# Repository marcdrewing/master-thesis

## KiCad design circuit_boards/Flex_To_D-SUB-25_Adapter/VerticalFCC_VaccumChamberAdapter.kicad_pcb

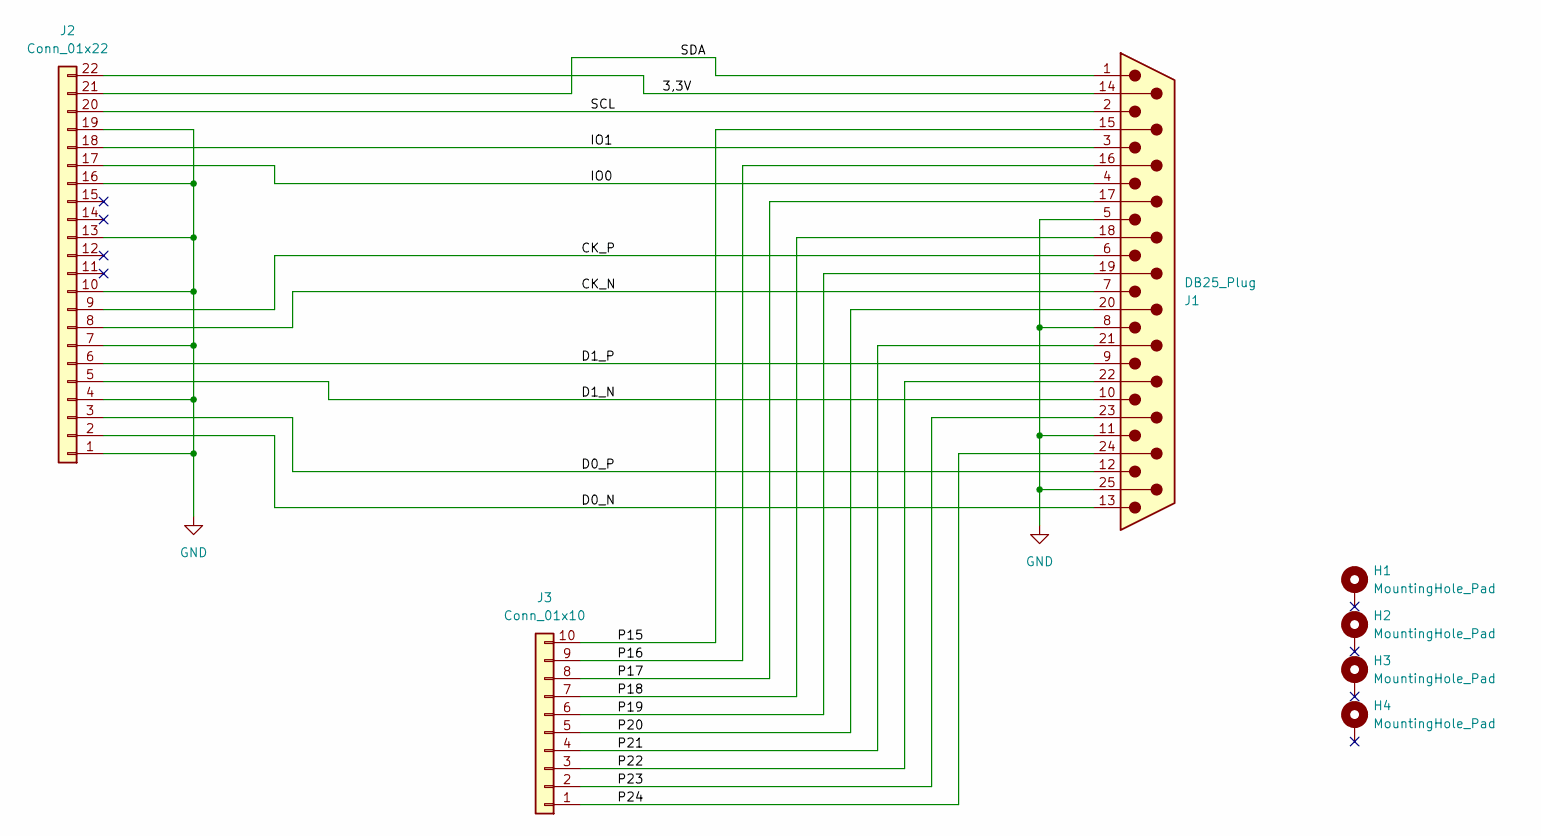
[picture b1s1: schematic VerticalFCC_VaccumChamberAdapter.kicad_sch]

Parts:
H1, H2, H3, H4: MountingHole_Pad; MountingHole_2.5mm_Pad
J1: DB25_Plug; D-Sub 25 Platine Buchse
J2: Conn_01x22; 22P 0.5mm Vertical FPC FFC Flat Cable Connector
J3: Conn_01x10; PinHeader_1x10_P2.54mm_Vertical

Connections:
/3,3V: J1.14, J2.22
/CK_N: J1.7, J2.8
/CK_P: J1.6, J2.9
/D0_N: J1.13, J2.2
/D0_P: J1.12, J2.3
/D1_N: J1.10, J2.5
/D1_P: J1.9, J2.6
/IO0: J1.4, J2.17
/IO1: J1.3, J2.18
/P15: J1.15, J3.10
/P16: J1.16, J3.9
/P17: J1.17, J3.8
/P18: J1.18, J3.7
/P19: J1.19, J3.6
/P20: J1.20, J3.5
/P21: J1.21, J3.4
/P22: J1.22, J3.3
/P23: J1.23, J3.2
/P24: J1.24, J3.1
/SCL: J1.2, J2.20
/SDA: J1.1, J2.21
GND: J1.5, J1.8, J1.11, J1.25, J2.1, J2.4, J2.7, J2.10, J2.13, J2.16, J2.19

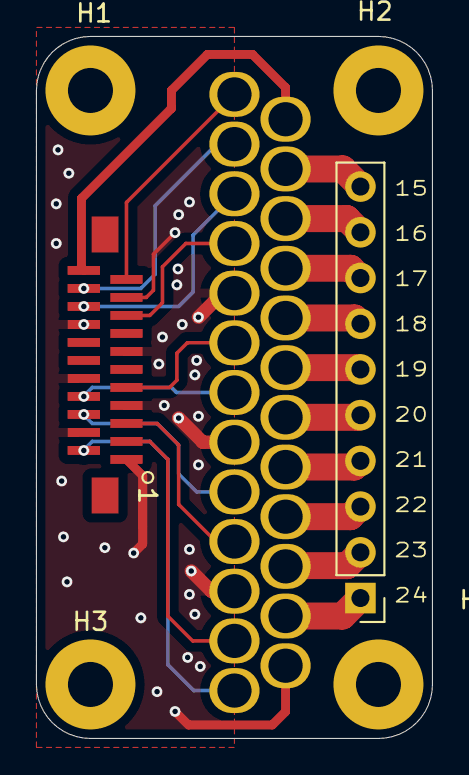
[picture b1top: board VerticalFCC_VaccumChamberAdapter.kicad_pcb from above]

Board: 2 copper layers, 22.0 x 39.0 mm, 7 parts (0 on the bottom side), 22 nets.

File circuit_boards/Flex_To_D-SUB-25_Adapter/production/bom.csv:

Designator,Footprint,Quantity,Value,LCSC Part #
J1,D-Sub 25 Platine Buchse,1,DB25_Plug,
J2,22P 0.5mm Vertical FPC FFC Flat Cable Connector,1,Conn_01x22,
J3,PinHeader_1x10_P2.54mm_Vertical,1,Conn_01x10,

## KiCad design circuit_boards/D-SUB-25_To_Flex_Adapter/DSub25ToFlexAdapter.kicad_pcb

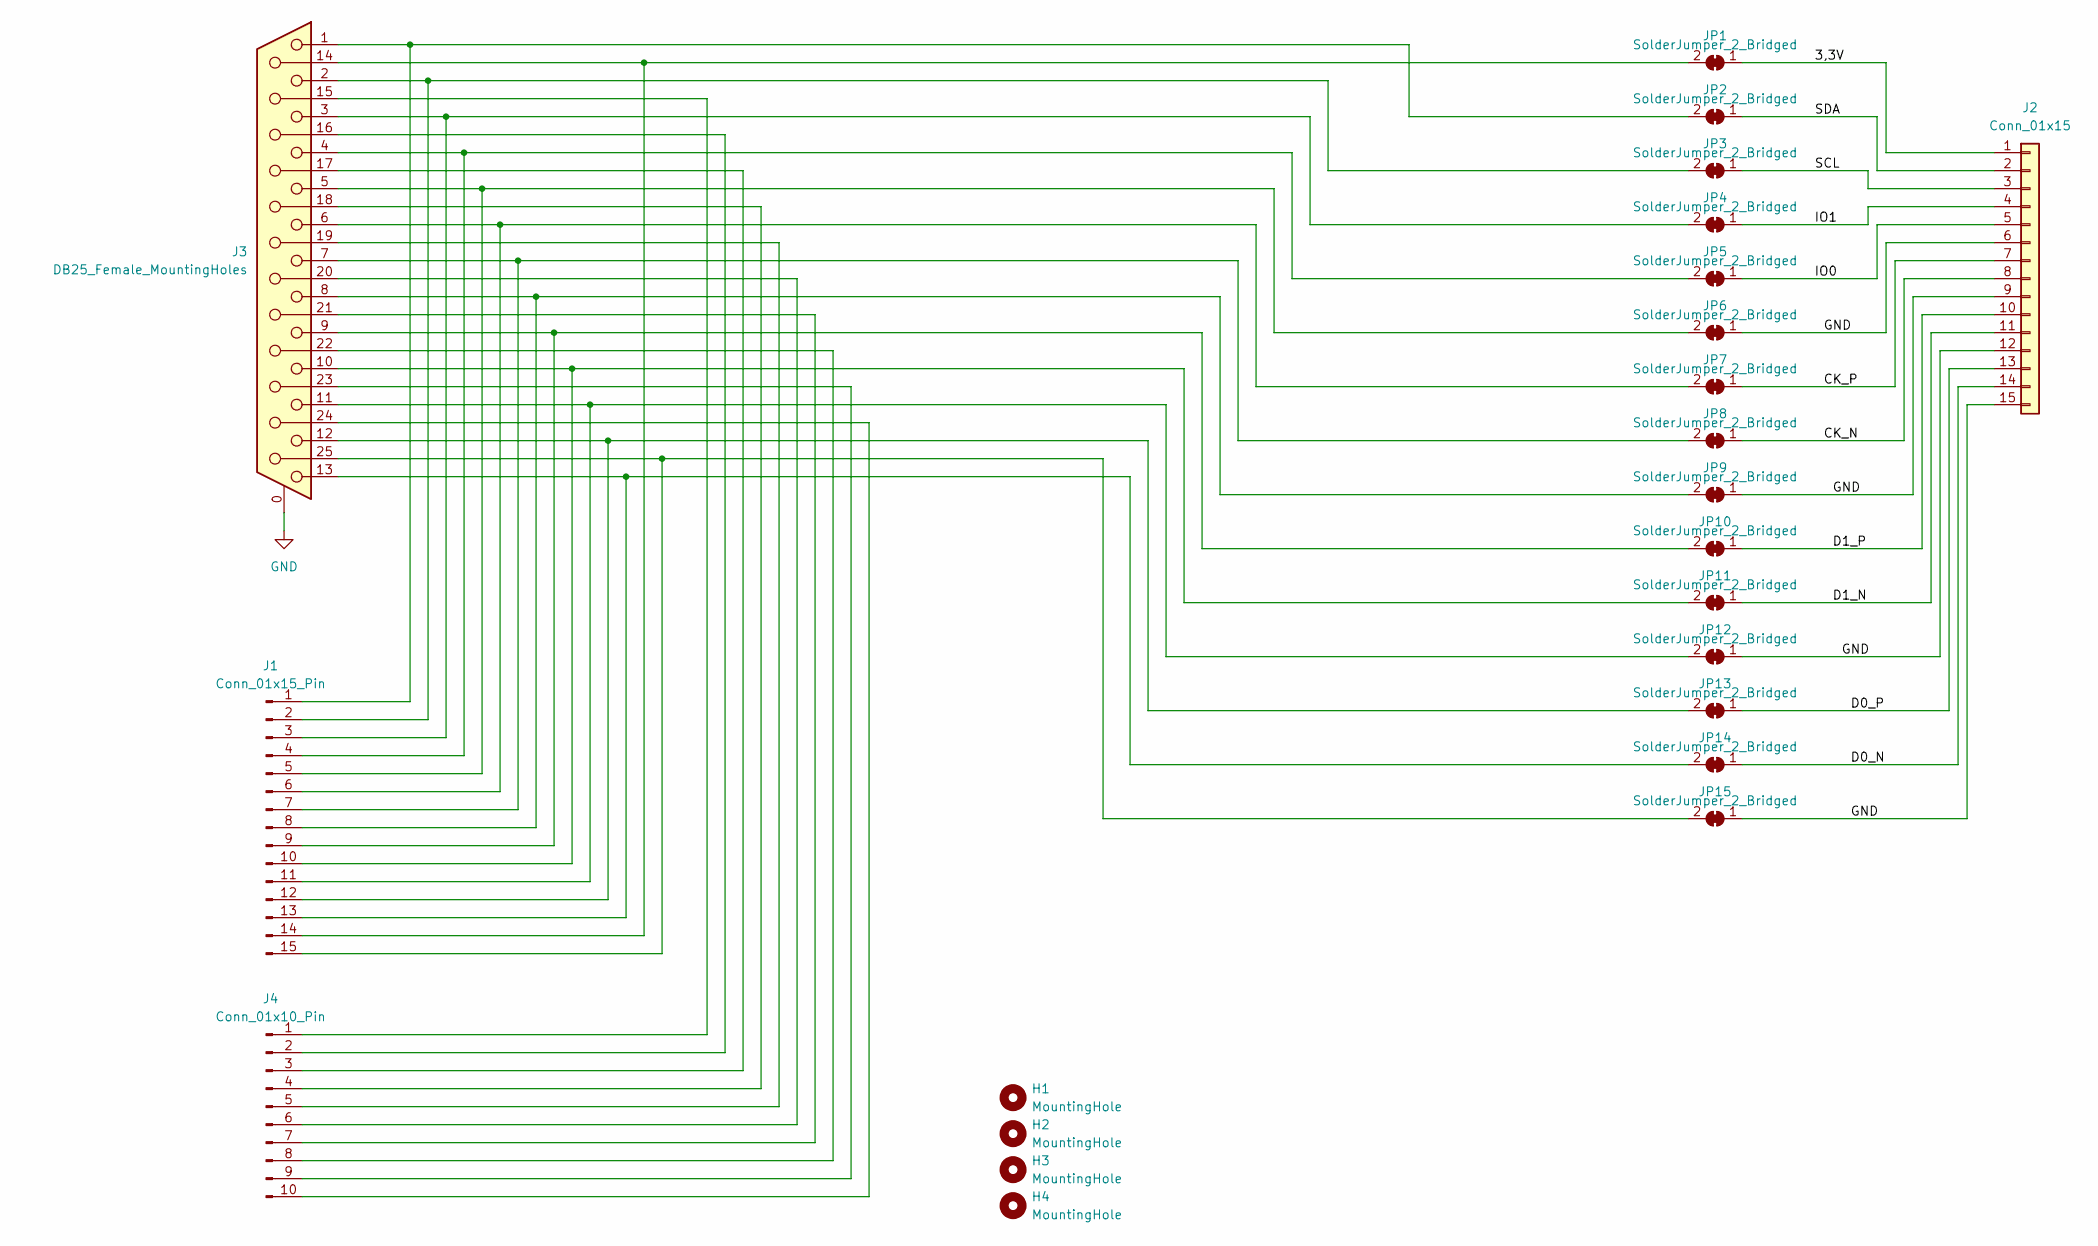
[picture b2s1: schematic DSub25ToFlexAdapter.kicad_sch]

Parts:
H1, H2, H3, H4: MountingHole; MountingHole_3.2mm_M3_DIN965_Pad
J1: Conn_01x15_Pin; PinHeader_1x15_P2.54mm_Vertical
J2: Conn_01x15; 15P 1mm FPC FFC Flat Cable Connector
J3: DB25_Female_MountingHoles; DSUB-25_Female_Horizontal_P2.77x2.84mm_EdgePinOffset7.70mm_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
J4: Conn_01x10_Pin; PinHeader_1x10_P2.54mm_Vertical
JP1, JP2, JP3, JP4, JP5, JP6, JP7, JP8, JP9, JP10, JP11, JP12, JP13, JP14, JP15: SolderJumper_2_Bridged; SolderJumper-2_P1.3mm_Bridged_Pad1.0x1.5mm

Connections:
/3,3V: J2.1, JP1.1 (A)
/CK_N: J2.8, JP8.1 (A)
/CK_P: J2.7, JP7.1 (A)
/D0_N: J2.14, JP14.1 (A)
/D0_P: J2.13, JP13.1 (A)
/D1_N: J2.11, JP11.1 (A)
/D1_P: J2.10, JP10.1 (A)
/IO0: J2.5, JP5.1 (A)
/IO1: J2.4, JP4.1 (A)
/SCL: J2.3, JP3.1 (A)
/SDA: J2.2, JP2.1 (A)
GND: J2.6, J2.9, J2.12, J2.15, J3.0 (PAD), JP6.1 (A), JP9.1 (A), JP12.1 (A), JP15.1 (A)
unnamed: J1.1, J3.1, JP2.2 (B)
unnamed: J1.2, J3.2, JP3.2 (B)
unnamed: J1.3, J3.3, JP4.2 (B)
unnamed: J1.4, J3.4, JP5.2 (B)
unnamed: J1.5, J3.5, JP6.2 (B)
unnamed: J1.6, J3.6, JP7.2 (B)
unnamed: J1.7, J3.7, JP8.2 (B)
unnamed: J1.8, J3.8, JP9.2 (B)
unnamed: J1.9, J3.9, JP10.2 (B)
unnamed: J1.10, J3.10, JP11.2 (B)
unnamed: J1.11, J3.11, JP12.2 (B)
unnamed: J1.12, J3.12, JP13.2 (B)
unnamed: J1.13, J3.13, JP14.2 (B)
unnamed: J1.14, J3.14, JP1.2 (B)
unnamed: J1.15, J3.25, JP15.2 (B)
unnamed: J3.15, J4.1
unnamed: J3.16, J4.2
unnamed: J3.17, J4.3
unnamed: J3.18, J4.4
unnamed: J3.19, J4.5
unnamed: J3.20, J4.6
unnamed: J3.21, J4.7
unnamed: J3.22, J4.8
unnamed: J3.23, J4.9
unnamed: J3.24, J4.10

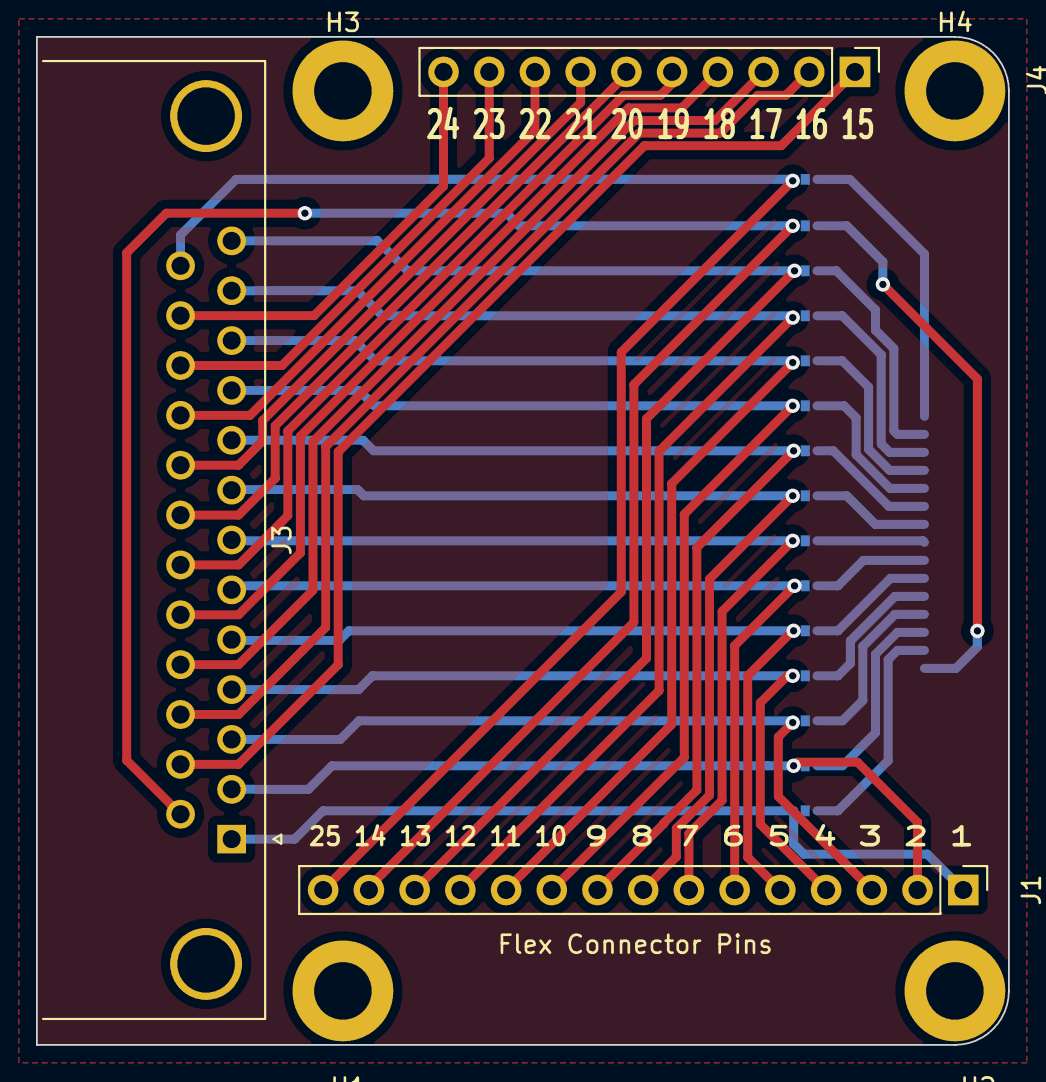
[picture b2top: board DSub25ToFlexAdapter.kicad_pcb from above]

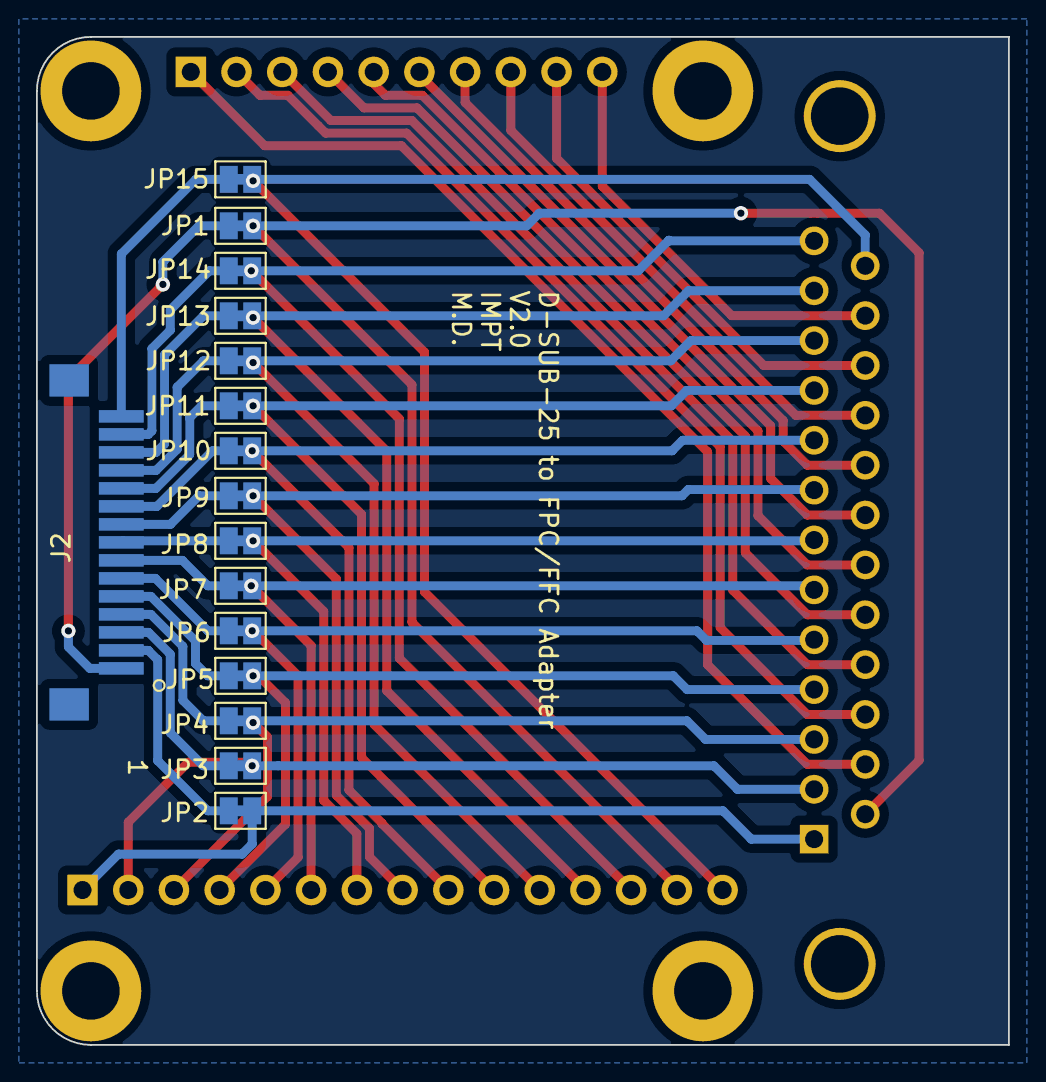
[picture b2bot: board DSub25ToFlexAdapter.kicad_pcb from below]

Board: 2 copper layers, 54.0 x 56.0 mm, 23 parts (16 on the bottom side), 37 nets.

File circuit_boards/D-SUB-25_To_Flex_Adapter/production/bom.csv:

Designator,Footprint,Quantity,Value,LCSC Part #
"H1, H2, H3, H4",MountingHole_3.2mm_M3_DIN965_Pad,4,MountingHole,
J1,PinHeader_1x15_P2.54mm_Vertical,1,Conn_01x15_Pin,
J2,15P 1mm FPC FFC Flat Cable Connector,1,Conn_01x15,
J3,DSUB-25_Female_Horizontal_P2.77x2.84mm_EdgePinOffset7.70mm_Housed_MountingHolesOffset9.12mm,1,DB25_Female_MountingHoles,
J4,PinHeader_1x10_P2.54mm_Vertical,1,Conn_01x10_Pin,
"JP1, JP10, JP11, JP12, JP13, JP14, JP15, JP2, JP3, JP4, JP5, JP6, JP7, JP8, JP9",SolderJumper-2_P1.3mm_Bridged_Pad1.0x1.5mm,15,SolderJumper_2_Bridged,

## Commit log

2025-10-26 Update evaluateModel.py
    fixed a change that was made when switching from predicting to detecting
